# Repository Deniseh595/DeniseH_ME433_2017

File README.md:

# DeniseH_ME433_2017

433 HWs and projs

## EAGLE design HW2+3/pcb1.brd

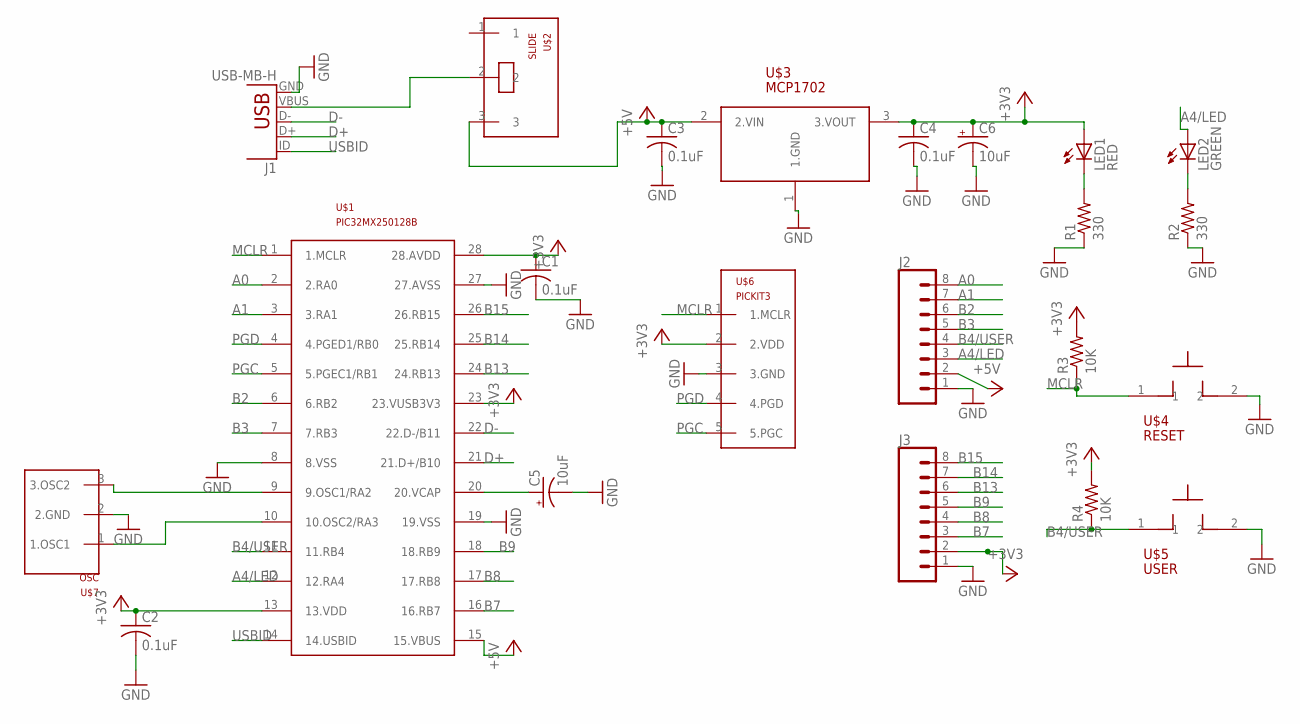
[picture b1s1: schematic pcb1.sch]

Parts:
C1, C2, C3, C4: 0.1uF; C025-025X050
C5, C6: 10uF; B45181A
J1: USB-MB-H
J2, J3: CONN_08"; 1X08
LED1: RED; LED3MM
LED2: GREEN; LED3MM
R1, R2: 330; 0207/10
R3, R4: 10K; 0207/10
U$1: PIC32MX250128B; DIL28-3
U$2: SLIDE
U$3: MCP1702; TO92
U$4: RESET; PB
U$5: USER; PB
U$6: PICKIT3; 1X05
U$7: OSC

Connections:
+3V3: C1.1, C2.1, C4.1, C6.+, J3.2, LED1.A, R3.2, R4.2, U$1.13 (13.VDD), U$1.23 (23.VUSB3V3), U$1.28 (28.AVDD), U$3.3 (3.VOUT), U$6.2 (2.VDD)
+5V: C3.1, J2.2, U$1.15 (15.VBUS), U$2.3, U$3.2 (2.VIN)
A0: J2.8, U$1.2 (2.RA0)
A1: J2.7, U$1.3 (3.RA1)
A4/LED: J2.3, LED2.A, U$1.12 (12.RA4)
B2: J2.6, U$1.6 (6.RB2)
B3: J2.5, U$1.7 (7.RB3)
B4/USER: J2.4, R4.1, U$1.11 (11.RB4), U$5.1
B7: J3.3, U$1.16 (16.RB7)
B8: J3.4, U$1.17 (17.RB8)
B9: J3.5, U$1.18 (18.RB9)
B13: J3.6, U$1.24 (24.RB13)
B14: J3.7, U$1.25 (25.RB14)
B15: J3.8, U$1.26 (26.RB15)
D+: J1.D+, U$1.21 (21.D+/B10)
D-: J1.D-, U$1.22 (22.D-/B11)
GND: C1.2, C2.2, C3.2, C4.2, C5.-, C6.-, J1.GND, J2.1, J3.1, R1.1, R2.1, U$1.8 (8.VSS), U$1.19 (19.VSS), U$1.27 (27.AVSS), U$3.1 (1.GND), U$4.2, U$5.2, U$6.3 (3.GND), U$7.2 (2.GND)
MCLR: R3.1, U$1.1 (1.MCLR), U$4.1, U$6.1 (1.MCLR)
unnamed: J1.VBUS, U$2.2
unnamed: U$1.9 (9.OSC1/RA2), U$7.3 (3.OSC2)
unnamed: LED1.K (C), R1.2
unnamed: U$1.10 (10.OSC2/RA3), U$7.1 (1.OSC1)
unnamed: C5.+, U$1.20 (20.VCAP)
unnamed: LED2.K (C), R2.2
PGC: U$1.5 (5.PGEC1/RB1), U$6.5 (5.PGC)
PGD: U$1.4 (4.PGED1/RB0), U$6.4 (4.PGD)
USBID: J1.ID, U$1.14 (14.USBID)

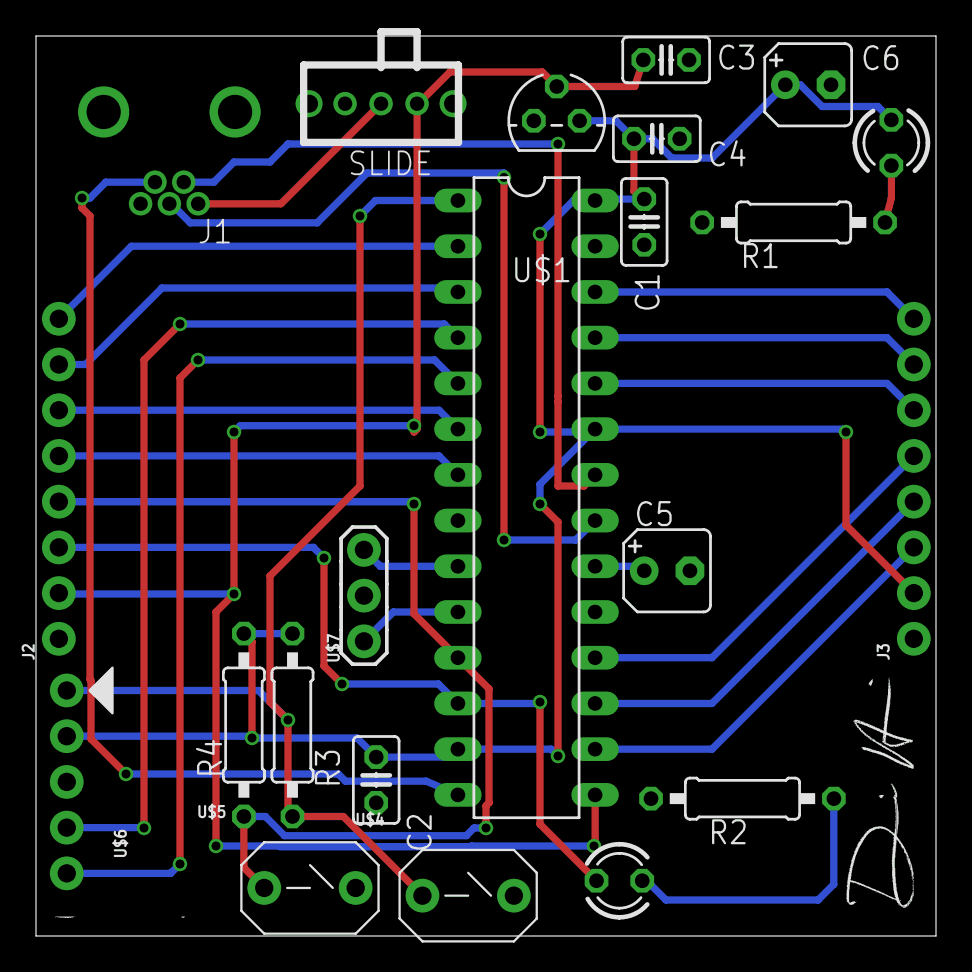
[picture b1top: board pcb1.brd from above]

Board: 2 copper layers, 50.0 x 50.0 mm, 22 parts (0 on the bottom side), 27 nets.

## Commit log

2017-03-30 LEDon
2017-03-30 FinalcodeandimgsHW1
2017-03-30 FinalHW1
2017-03-30 Real Final HW1
    Added push button command
2017-04-07 HW2
    library and schematic
2017-04-07 brd
    first try of layout - pre error check
2017-04-07 Made a pcb
    made some gerber files
2017-04-10 Name Update
    Includes both HW2 & 3
2017-04-16 HW 4 - SPI
2017-04-17 Finished HW 4 SPI
2017-04-21 Update for HW 5 - I2C
2017-04-23 hw5 update
2017-04-23 hw 6 done -
2017-04-24 HW updates - up to LCD
2017-04-26 hw7code update
2017-04-29 IMU update
2017-04-30 IMU Done
2017-04-30 HW1 works with Harmony
2017-05-01 HW8 done
2017-05-11 HW updates - 12 done, work on 11
2017-05-14 Found the color green
2017-05-15 back to HW 9
2017-05-25 CADstuff
2017-05-30 Code updates
2017-06-08 Newcodes
2017-06-08 HW14 merged
2017-06-08 working hw 14
2017-06-08 Android code added to USB
2017-06-09 Motor control used in final project
2017-06-11 Moved codes to tech cup folder
    added car pic
